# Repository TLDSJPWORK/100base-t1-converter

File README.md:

# 100base-t1-converter for Education
学習用 100Base-T1 MediaConnverter

### 特徴
- NXP社のTJA1101とCoreChips社のSR8201F（Realtek社 RTL8201F互換）を使用した 100Base-T1 <-> 100Base-TX のMediaConverterです。
- STM32F103C8T6を搭載したBlue Pill[参考URL](https://en.wikipedia.org/wiki/STM32)を使うことでPHYの設定をMDIOを用いて確認／実施することができ、PHY層の動きを学習することができます。
- オリジナルは Creative Commons Attribution-ShareAlike 4.0 International ライセンスで公開されている[100base-t1-converter](https://github.com/ehntoo/100base-t1-converter)です。作者はehntoo様です。
- 本プロダクトはベースプロダクトから、MDIOでPHYの設定を読み書きするプログラムを追加し、また、[LCSC](https://www.lcsc.com/)で部品を注文するための具体的な部品番号の追加および部品配置の変更と、基板を[JLCPCB](https://jlcpcb.com/)でより安く注文できるように最小ドリル径を変更したものとなります。
- 本プロダクトのライセンスは Creative Commons Attribution-ShareAlike 4.0 International を継承します。

### 基板

（※基盤イメージ／写真は参考であり、改良のため変更することがあります）

### 基板の設定

### 使用例
- メディアコンバータとして利用するだけならば、下記ジャンパの設定で、Blue Pillとそれに書き込むソフトウェアの対応は不要です。

- Blue Pillにソフトウェアを書き込むことで、MDIOを通してPYHチップの動作確認、変更が可能です。

[レジスター読み書きソフト](/software/phyRegRead/)

- Blue PillをArduinoとして利用し、上記ソフトを書き込むことで、レジスターの読み書きができます。

（ch1がPB7のMDC(Clock)、ch2がPB6のMDIO(Data)です）

- PHYADDR：TJA1101=0x06, SR8201F=0x02
- シリアルコマンド：a 送信=全レジスタ読み出し, r (phyaddr) (register number) 送信=指定レジスタ読出, w (phyaddr) (register number) (レジスタ値) 送信=指定レジスタ書込

### 販売ページ

- スイッチサイエンス様

### 資料

- [サポートページ](https://github.com/TLDSJPWORK/100base-t1-converter)
- [回路図](docs/100base-t1-converter.pdf)
- [TJA1101データシート](https://www.nxp.com/docs/en/data-sheet/TJA1101B.pdf)
- [SR8201Fデータシート](https://www.lcsc.com/datasheet/lcsc_datasheet_2409272302_CoreChips-SR8201F_C378491.pdf) 
- [Blue Pill](https://en.wikipedia.org/wiki/STM32)
- [STM32F103 ボードを Arduino ライクに使う](https://ht-deko.com/arduino/stm32f103c8t6.html)
- [MDIOとは | Ethernet(イーサネット)技術コラム](https://www.e-nexty.com/static/articles/column_ethernet_mdio)

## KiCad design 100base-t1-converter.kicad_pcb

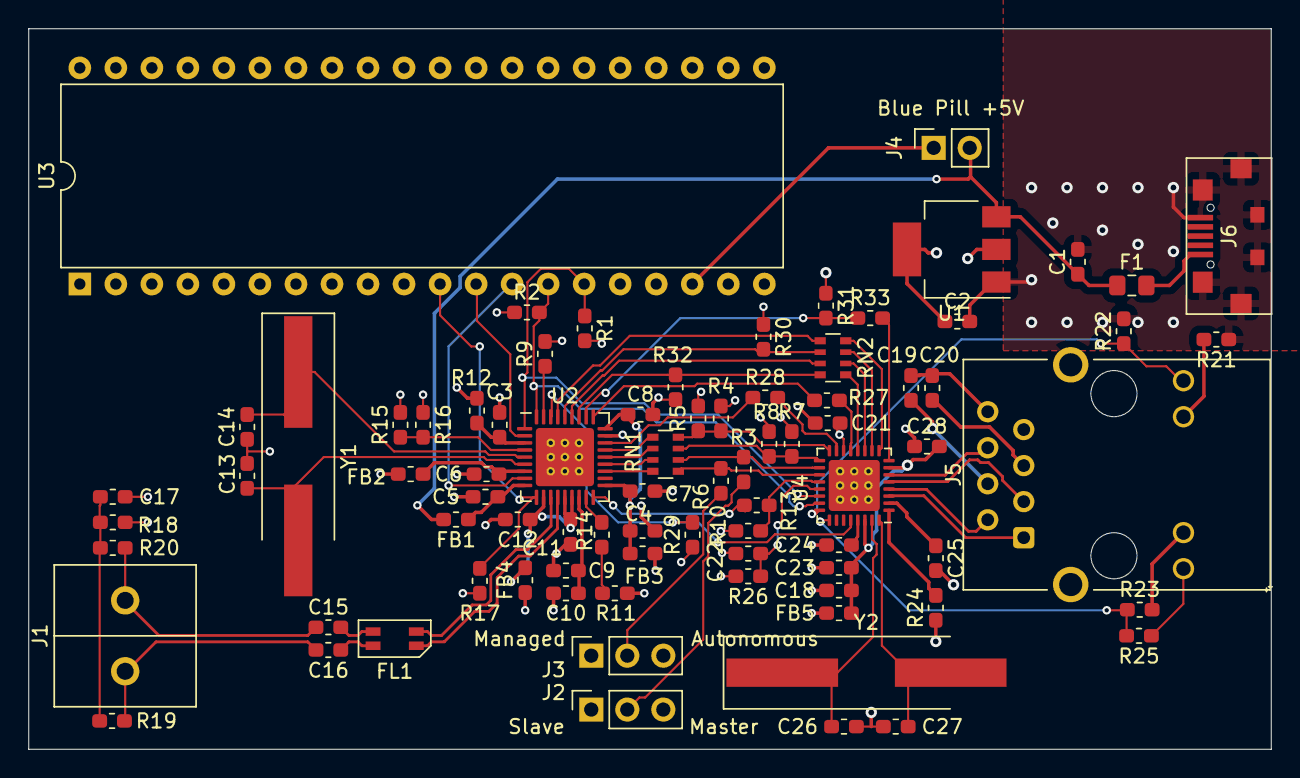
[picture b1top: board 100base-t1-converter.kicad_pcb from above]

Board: 4 copper layers, 87.6 x 50.8 mm, 82 parts (0 on the bottom side), 50 nets.

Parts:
C1, C2, C4, C18: 10uF; C_0603_1608Metric_Pad1.05x0.95mm_HandSolder
C3, C5, C7, C8, C11, C12, C15, C16, C19, C20, C21, C22, C23, C24, C25, C28: 0.1uF; C_0603_1608Metric_Pad1.05x0.95mm_HandSolder
C6, C9, C10: 0.47uF; C_0603_1608Metric_Pad1.05x0.95mm_HandSolder
C13, C14, C26, C27: 27pF; C_0603_1608Metric_Pad1.05x0.95mm_HandSolder
C17: 4700pF; C_0603_1608Metric_Pad1.05x0.95mm_HandSolder
F1: 500mA; Fuse_0805_2012Metric_Pad1.15x1.40mm_HandSolder
FB1, FB3: 120R; L_0603_1608Metric_Pad1.05x0.95mm_HandSolder
FB2, FB4: 0; L_0603_1608Metric_Pad1.05x0.95mm_HandSolder
FB5: BLM18PG181SN1D; L_0603_1608Metric_Pad1.05x0.95mm_HandSolder
FL1: ACT1210L-201-2P-TL00; SOIC-4
J1: Conn_01x02; SIP-2
J2, J3: Conn_01x03; PinSocket_1x03_P2.54mm_Vertical
J4: Conn_01x02; PinSocket_1x02_P2.54mm_Vertical
J5: 8P8C_LED_Shielded; RJ45_Hanrun_HR911105A
J6: USB_B_Micro; LCSC_C77238
R1, R2, R3, R6, R10, R11, R12, R22, R25, R26, R29, R30, R31, R32: 4.7k; R_0603_1608Metric_Pad1.05x0.95mm_HandSolder
R4, R5, R7, R8, R16: DNP; R_0603_1608Metric_Pad1.05x0.95mm_HandSolder
R9, R15: 10k; R_0603_1608Metric_Pad1.05x0.95mm_HandSolder
R13, R14, R27, R28, R33: 33; R_0603_1608Metric_Pad1.05x0.95mm_HandSolder
R17, R18: 100k; R_0603_1608Metric_Pad1.05x0.95mm_HandSolder
R19, R20: 1.0k; R_0603_1608Metric_Pad1.05x0.95mm_HandSolder
R21, R23: 510; R_0603_1608Metric_Pad1.05x0.95mm_HandSolder
R24: 2.49k 1%; R_0603_1608Metric_Pad1.05x0.95mm_HandSolder
RN1: 33; R_Array_Convex_Reversed_4x0603
RN2: 33R; R_Array_Convex_Reversed_4x0603
U1: AP1117-33; SOT-223-3_TabPin2
U2: TJA1101; QFN-36-1EP_6x6mm_P0.5mm_EP4.1x4.1mm_ThermalVias
U3: blue_pill; DIP-40_W15.24mm
U4: SR8201F; QFN-32-1EP_5x5mm_P0.5mm_EP3.6x3.6mm_ThermalVias
Y1, Y2: TXC 9C25000026; Crystal_SMD_HC49-SD_HandSoldering

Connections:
+3V3: C2.1, C21.2, FB2.2, FB3.2, FB4.1, FB5.2, J2.3, J3.3, J5.9, R1.2, R2.1, R5.2, R8.2, R9.2, R10.1, R11.1, R12.2, R16.1, R25.1, R26.2, U1.2 (VO), U4.14 (DVDD33)
+5V: C1.1, F1.1, FB1.2, J4.2, U1.3 (VI)
/TRX+: C15.1, J1.1, R20.2
/TRX-: C16.2, J1.2, R19.2
/micro/INH: R17.1, U2.10 (INH), U3.11 (PB3)
/micro/MDC: R1.1, U2.1 (MDC), U3.15 (PB7), U4.22 (MDC)
/micro/MDIO: R2.2, U2.36 (MDIO), U3.14 (PB6), U4.23 (MDIO)
/micro/WAKE_IN_OUT: U2.8 (WAKE_IN_OUT), U3.13 (PB5)
/micro/~INT: U2.2 (~INT), U3.12 (PB4)
/tja1101/CHIP_TRX+: FL1.2, U2.12 (TRX_P)
/tja1101/CHIP_TRX-: FL1.1, U2.13 (TRX_M)
/tja1101/CMC_TRX+: C15.2, FL1.3
/tja1101/CMC_TRX-: C16.1, FL1.4
/tja1101/RXC: R28.1, U2.25 (RXC/REF_CLK)
/tja1101/RXD0: R4.1, R5.1, RN1.1 (R1.1), U4.16 (TXD[0])
/tja1101/RXD1: R7.1, R8.1, RN1.2 (R2.1), U4.17 (TXD[1])
/tja1101/RXD2: R3.2, RN1.3 (R3.1), U4.18 (TXD[2])
/tja1101/RXD3: R6.2, RN1.4 (R4.1), U4.19 (TXD[3])
/tja1101/RXDV: R10.2, R13.2, U4.20 (TXEN)
/tja1101/RXER: R11.2, R14.2
/tja1101/TXC: R27.1, U2.28 (TXC)
/tja1101/TXD0: RN2.8 (R1.2), U2.33 (TXD0)
/tja1101/TXD1: R30.2, RN2.7 (R2.2), U2.32 (TXD1)
/tja1101/TXD2: RN2.6 (R3.2), U2.31 (TXD2)
/tja1101/TXD3: R32.2, RN2.5 (R4.2), U2.30 (TXD3)
/tja1101/TXEN: R31.2, R33.1, U2.29 (TXEN)
/tja1101/TXER: R29.2, U2.34 (TXER), U4.28 (RXER/FXEN)
/tx_mac/MDI0+: J5.1 (TD+), U4.3 (MDI+[0])
/tx_mac/MDI0-: J5.2 (TD-), U4.4 (MDI-[0])
/tx_mac/MDI1+: J5.3 (RD+), U4.5 (MDI+[1])
/tx_mac/MDI1-: J5.6 (RD-), U4.6 (MDI-[1])
GND: C1.2, C2.2, C3.2, C4.1, C5.1, C6.1, C7.1, C8.2, C9.1, C10.1, C11.1, C12.2, C13.1, C14.1, C17.2, C18.1, C19.1, C20.1, C21.1, C22.2, C23.1, C24.1, C25.2, C26.1, C27.1, C28.1, J2.1, J3.1, J5.8 (GND), J5.SH, J6.5 (GND), J6.6 (Shield), R4.2, R7.2, R15.2, R17.2, R18.1, R21.1, R22.2, R24.1, R29.1, R30.1, R31.1, R32.1, U1.1 (GND), U2.26 (GND), U2.37 (EP), U3.19 (GND), U3.39 (GND), U3.40 (GND), U4.33 (GND)
unnamed: C3.1, R12.1, U2.3 (~RST)
unnamed: C13.2, U2.6 (XI), Y1.2
unnamed: C14.2, U2.5 (XO), Y1.1
unnamed: C6.2, FB2.1, U2.7 (VDDA_3V3)
unnamed: C11.2, C12.1, FB4.2, U2.11 (VDDA_TX1), U2.14 (VDDA_TX2), U2.15 (VDDD_3V3)
unnamed: F1.2, J6.1 (VBUS)
unnamed: C25.1, U4.2 (AVDD10OUT)
unnamed: C26.2, U4.31 (CKXTAL1), Y2.1
unnamed: C27.2, U4.32 (CKXTAL2), Y2.2
unnamed: C24.2, U4.29 (DVDD10OUT)
unnamed: R23.1, R25.2, U4.25 (LED1/PHYAD[1])
unnamed: J5.12, R22.1, U4.24 (PHYAD[0]/LED0/PMEB)
unnamed: C22.1, R26.1, U4.21 (PHYRSTB)
unnamed: R24.2, U4.1 (RSET)
unnamed: R27.2, U4.13 (RXC)
unnamed: R33.2, U4.8 (RXDV)
unnamed: R28.2, U4.15 (TXC)
VDDA: C18.2, C23.2, C28.2, FB5.1, U4.7 (AVDD33), U4.30 (AVDD33)

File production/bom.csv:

Designator,Footprint,Quantity,Value,LCSC Part #
"C1, C18, C2, C4",603,4,10uF,C96446
"C10, C6, C9",603,3,0.47uF,C1623
"C11, C12, C15, C16, C19, C20, C21, C22, C23, C24, C25, C28, C3, C5, C7, C8",603,16,0.1uF,C14663
"C13, C14, C26, C27",603,4,27pF,C1647
C17,603,1,4700pF,C53987
F1,805,1,500mA,C516070
"FB1, FB3",603,2,120R,C22787
"FB2, FB4",603,2,0,
FB5,603,1,BLM18PG181SN1D,C82850
FL1,SOIC-4,1,ACT1210L-201-2P-TL00,C131444
J1,SIP-2,1,Conn_01x02,
"J2, J3",PinSocket_1x03_P2.54mm_Vertical,2,Conn_01x03,
J4,PinSocket_1x02_P2.54mm_Vertical,1,Conn_01x02,
J5,RJ45_Hanrun_HR911105A,1,8P8C_LED_Shielded,C12074
J6,LCSC_C77238,1,USB_B_Micro,C77238
"R1, R10, R11, R12, R2, R22, R25, R26, R29, R3, R30, R31, R32, R6",603,14,4.7k,C23162
"R13, R14, R27, R28, R33",603,5,33,C23140
"R15, R9",603,2,10k,C25804
"R16, R4, R5, R7, R8",603,5,DNP,
"R17, R18",603,2,100k,C25803
"R19, R20",603,2,1.0k,C21190
"R21, R23",603,2,510,C23193
R24,603,1,2.49k 1%,C108190
RN1,R_Array_Convex_Reversed_4x0603,1,33,C25508
RN2,R_Array_Convex_Reversed_4x0603,1,33R,C25508
U1,SOT-223-3_TabPin2,1,AP1117-33,C115288
U2,QFN-36-1EP_6x6mm_P0.5mm_EP4.1x4.1mm_ThermalVias,1,TJA1101,C2671511
U3,DIP-40_W15.24mm,1,blue_pill,
U4,QFN-32-1EP_5x5mm_P0.5mm_EP3.6x3.6mm_ThermalVias,1,SR8201F,C378491
"Y1, Y2",Crystal_SMD_HC49-SD_HandSoldering,2,TXC 9C25000026,C2890202

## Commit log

2025-05-26 JPWORK modify commit
2025-05-27 Mod README.md
2025-05-27 スペル誤りの修正
2025-06-02 誤字修正

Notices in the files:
100base-t1-converter.kicad_pcb:
Copyright JP WORKS 2025
Licensed CC-BY-SA
